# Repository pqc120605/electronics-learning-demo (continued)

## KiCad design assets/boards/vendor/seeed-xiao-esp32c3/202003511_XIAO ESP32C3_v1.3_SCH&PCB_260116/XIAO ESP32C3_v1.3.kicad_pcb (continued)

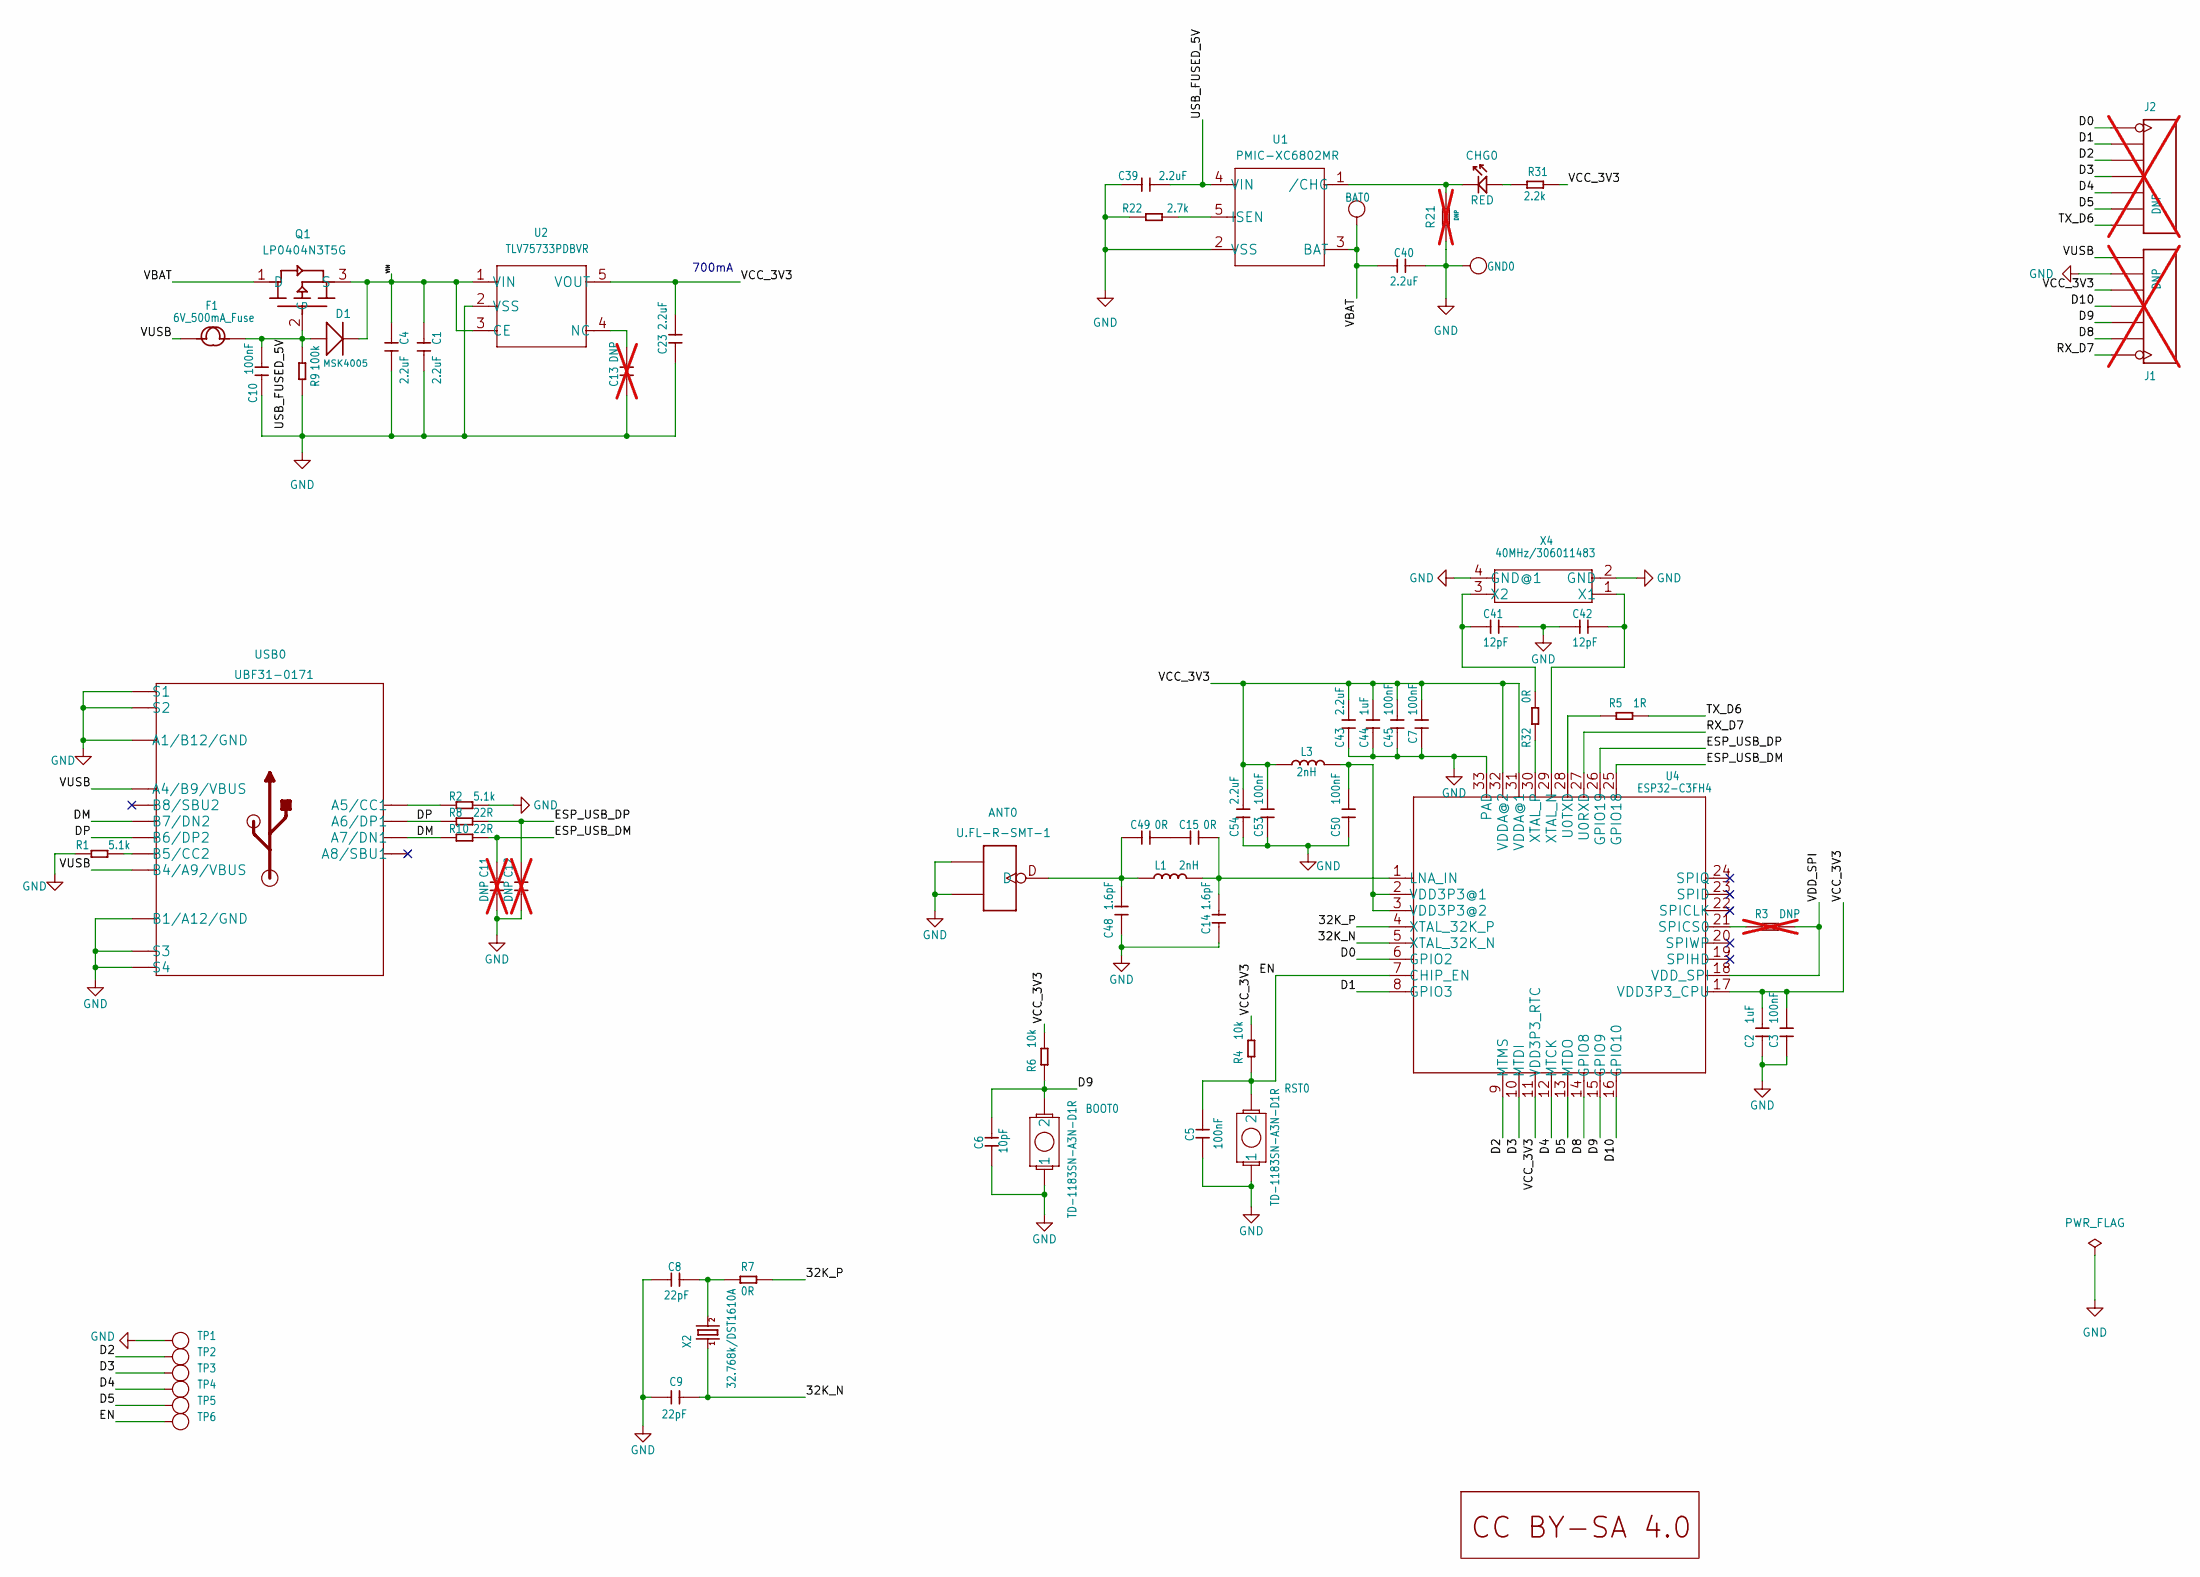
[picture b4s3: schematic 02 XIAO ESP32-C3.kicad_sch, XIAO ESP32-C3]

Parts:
ANT0: U.FL-R-SMT-1; U-FL3P-SMD-2.6X2.6X1.0MM
BAT0: DNP; TP-80X40MIL
BOOT0: TD-1183SN-A3N-D1R; BUTTON_TD1183SA
C1, C4, C23, C39, C40, C43, C54: 2.2uF; C0201
C2, C44: 1uF; C0201
C3, C5, C7, C10, C45, C50, C53: 100nF; C0201
C6: 10pF; C0201
C8, C9: 22pF; C0201
C11, C12, C13: DNP; C0201; not fitted
C14, C48: 1.6pF; C0201
C15, C49: 0R; C0201
C41, C42: 12pF; C0201
CHG0: RED; LED-0402
D1: MSK4005; SOD-523
F1: 6V_500mA_Fuse; F0603
GND0: DNP; TP-80X40MIL
J1, J2: DNP; H7-HALF-HOLE-2.54; not fitted
L1, L3: 2nH; L0201
Q1: LP0404N3T5G; PMOS_1.0_0.6_0.35MM
R1, R2: 5.1k; R0201
R3, R21: DNP; R0201; not fitted
R4, R6: 10k; R0201
R5: 1R; R0201
R7, R32: 0R; R0201
R8, R10: 22R; R0201
R9: 100k; R0201
R22: 2.7k; R0201
R31: 2.2k; R0201
RST0: TD-1183SN-A3N-D1R; BUTTON_TD1183SA
TP1, TP2, TP3, TP4, TP5, TP6: DNP; TP-D45MIL
U1: PMIC-XC6802MR; SOT-25
U2: TLV75733PDBVR; SOT-25
U4: ESP32-C3FH4; QFN32G-0.5-5X5MM
U6: LOGO_CC_BY-SA_4.0
USB0: UBF31-0171; USB2.0-TYPE-C
X2: 32.768k/DST1610A; X2-SMD-1.6X1.0X0.5MM
X4: 40MHz/306011483; X4-SMD-2.0X1.6X0.5MM

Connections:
32K_N: C9.1, U4.5 (XTAL_32K_N), X2.1
32K_P: R7.1, U4.4 (XTAL_32K_P)
D0: J2.1, J2.13 (1), U4.6 (GPIO2)
D1: J2.2, J2.14 (2), U4.8 (GPIO3)
D2: J2.3, J2.15 (3), TP2.T, U4.9 (MTMS)
D3: J2.4, J2.16 (4), TP3.T, U4.10 (MTDI)
D4: J2.5, J2.17 (5), TP4.T, U4.12 (MTCK)
D5: J2.6, J2.18 (6), TP5.T, U4.13 (MTDO)
D8: J1.2, J1.14 (2), U4.14 (GPIO8)
D9: BOOT0.2, C6.2, J1.3, J1.15 (3), R6.1, U4.15 (GPIO9)
D10: J1.4, J1.16 (4), U4.16 (GPIO10)
DM: R10.1, USB0.A7 (A7/DN1), USB0.B7 (B7/DN2)
DP: R8.1, USB0.A6 (A6/DP1), USB0.B6 (B6/DP2)
EN: C5.2, R4.1, RST0.2, TP6.T, U4.7 (CHIP_EN)
ESP_USB_DM: C11.2, R10.2, U4.25 (GPIO18)
ESP_USB_DP: C12.2, R8.2, U4.26 (GPIO19)
GND: ANT0.GND1, ANT0.GND2, BOOT0.1, C1.2, C2.1, C3.1, C4.2, C5.1, C6.1, C7.1, C8.2, C9.2, C10.1, C11.1, C12.1, C13.1, C14.1, C23.1, C39.1, C40.2, C41.2, C42.2, C43.1, C44.1, C45.1, C48.1, C50.1, C53.1, C54.1, GND0.1, J1.6, J1.18 (6), R1.1, R2.2, R9.1, R21.2, R22.2, RST0.1, TP1.T, U1.2 (VSS), U2.2 (VSS), U4.33 (PAD), USB0.A1_B12 (A1/B12/GND), USB0.B1_A12 (B1/A12/GND), USB0.S1, USB0.S2, USB0.S3, USB0.S4, USB0.S5 (S1), USB0.S6 (S2), X4.2 (GND), X4.4 (GND@1)
unnamed: R2.1, USB0.A5 (A5/CC1)
unnamed: R1.2, USB0.B5 (B5/CC2)
unnamed: R3.1, U4.21 (SPICS0)
unnamed: C8.1, R7.2, X2.2
unnamed: C13.2, U2.4 (NC)
unnamed: C15.2, C49.1
unnamed: R22.1, U1.5 (ISEN)
unnamed: CHG0.+, R31.2
unnamed: C14.2, C15.1, L1.2, U4.1 (LNA_IN)
unnamed: C41.1, R32.2, X4.3 (X2)
unnamed: C42.1, U4.29 (XTAL_N), X4.1 (X1)
unnamed: ANT0.D, C48.2, C49.2, L1.1
unnamed: R5.2, U4.28 (U0TXD)
unnamed: C50.2, L3.2, U4.2 (VDD3P3@1), U4.3 (VDD3P3@2)
unnamed: R32.1, U4.30 (XTAL_P)
RX_D7: J1.1, J1.13 (1), U4.27 (U0RXD)
TX_D6: J2.7, J2.19 (7), R5.1
USB_FUSED_5V: C10.2, C39.2, D1.+, F1.2, Q1.2 (G), R9.2, U1.4 (VIN)
VBAT: BAT0.1, C40.1, Q1.1 (D), U1.3 (BAT)
VCC_3V3: C2.2, C3.2, C7.2, C23.2, C43.2, C44.2, C45.2, C53.2, C54.2, J1.5, J1.17 (5), L3.1, R4.2, R6.2, R31.1, U2.5 (VOUT), U4.11 (VDD3P3_RTC), U4.17 (VDD3P3_CPU), U4.31 (VDDA@1), U4.32 (VDDA@2)
VDD_SPI: R3.2, U4.18 (VDD_SPI)
VIN: C1.1, C4.1, D1.-, Q1.3 (S), U2.1 (VIN), U2.3 (CE)
VUSB: F1.1, J1.7, J1.19 (7), USB0.A4_B9 (A4/B9/VBUS), USB0.B4_A9 (B4/A9/VBUS)
~CHG: CHG0.-, R21.1, U1.1 (/CHG)

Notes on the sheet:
700mA

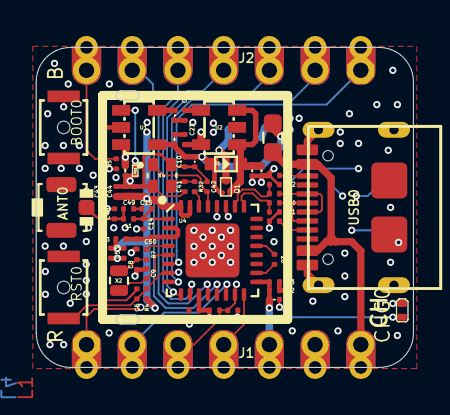
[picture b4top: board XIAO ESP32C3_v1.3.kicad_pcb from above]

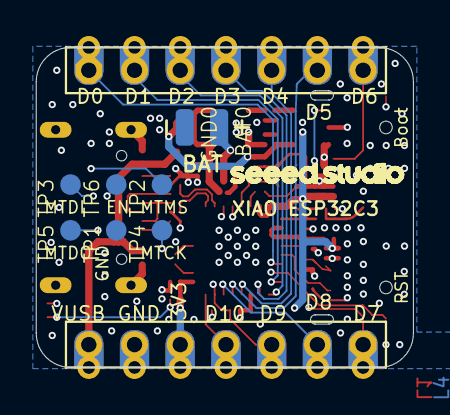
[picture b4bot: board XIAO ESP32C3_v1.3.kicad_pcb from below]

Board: 4 copper layers, 21.0 x 17.8 mm, 68 parts (9 on the bottom side), 41 nets.

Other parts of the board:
U$2: LOGO-SEEED-NEW-1X9.6MM

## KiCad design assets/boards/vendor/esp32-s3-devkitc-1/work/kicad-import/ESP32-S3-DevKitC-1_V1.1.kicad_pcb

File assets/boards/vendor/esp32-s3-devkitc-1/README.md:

# ESP32-S3-DevKitC-1 · PCB V1.1

The board catalog now includes an interactive educational 3D reconstruction of the official V1.1 reference layout.

- 48 CAD footprint/component groups have selectable package meshes.
- 44 J1/J3 header pads have selectable anchors and pinout details.
- BOM manufacturer part numbers are shown when the source BOM identifies them.
- Mesh identity, source coordinates, net-label provenance, and safety caveats are exposed in the board viewer.
- Most meshes are generic package shapes, not exact manufacturer-specific models.

The imported PADS board has DRC findings and unconnected items. The model is not physically validated, not a confirmed N8R8 build, and not suitable for fabrication or electrical sign-off. See [SOURCE.md](SOURCE.md) and the bundled [model notice](/models/esp32-s3-devkitc-1-v1.1.NOTICE.txt).

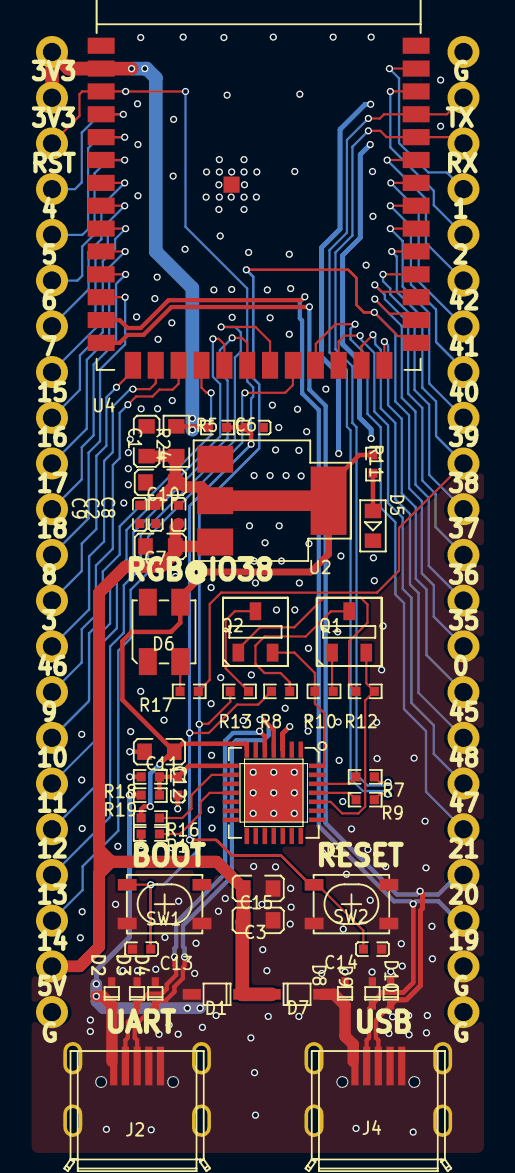
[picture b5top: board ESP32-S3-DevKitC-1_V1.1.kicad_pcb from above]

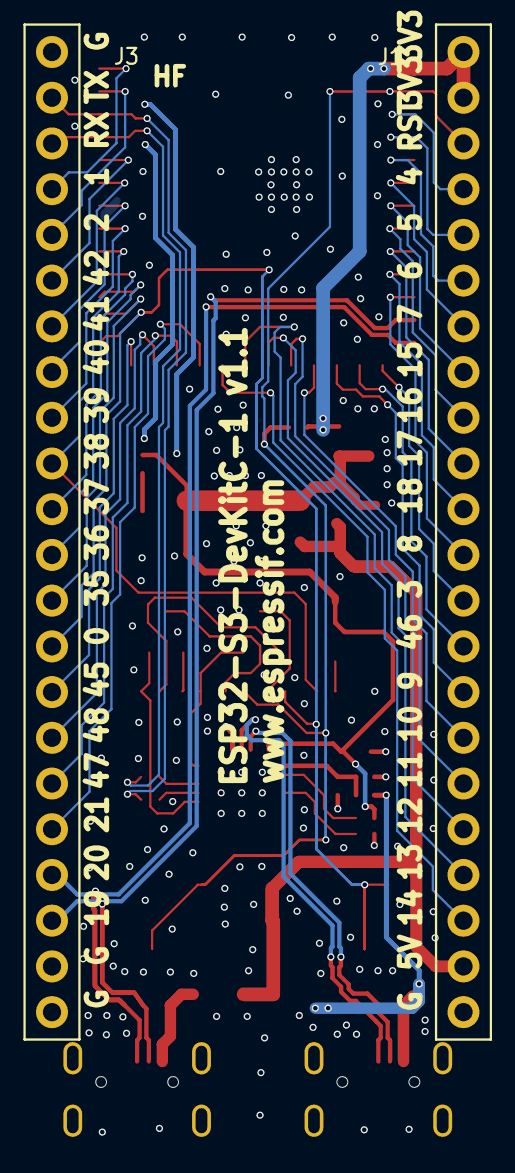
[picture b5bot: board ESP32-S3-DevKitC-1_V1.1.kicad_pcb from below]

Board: 2 copper layers, 48 parts (2 on the bottom side), 58 nets.

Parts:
C1, C3, C7, C10, C11, C15: C0603
C2, C6, C8, C9, C12, C13, C14: C0402
D1, D7: SOD123
D2, D3, D4, D8, D9, D10: SOD523
D5: LED0603
D6: LED3535B
J1, J3: CON22X1_2P54_OBLATE
J2, J4: USB_5P_MICRO_F_ML
Q1, Q2: SOT23-3
R5, R7, R8, R9, R10, R11, R12, R13, R14, R16, R17, R18, R19: R0402
R24: R0603
SW1, SW2: SW4-4P2X3P2X2P5-SMT
U2: SOT223
U3: QFN28_0P5_5
U4: ESP32-S3-WROOM_NEW

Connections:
CHIP_PU: C6.1, C14.2, J1.3, R5.1, R8.2, SW2.3, U4.3
D+: D4.2, J2.3, U3.4
D-: D3.2, J2.2, U3.5
DTR: Q2.2, R10.1, U3.28
ESP_3V3: J1.1, J1.2, R5.2, R24.2, U4.2
GND: C1.2, C2.2, C3.2, C6.2, C7.2, C8.2, C9.2, C10.2, C11.2, C12.2, C13.1, C14.1, C15.2, D2.1, D3.1, D4.1, D5.2, D6.1, D8.1, D9.1, D10.1, J1.22, J2.5, J2.6, J2.7, J2.8, J2.9, J3.1, J3.21, J3.22, J4.5, J4.6, J4.7, J4.8, J4.9, R14.2, R18.2, SW1.1, SW2.1, U2.1, U3.3, U3.29, U4.1, U4.40, U4.41
GPIO0: C13.2, J3.14, R13.2, SW1.3, U4.27
GPIO1: J3.4, U4.39
GPIO2: J3.5, U4.38
GPIO3: J1.13, U4.15
GPIO4: J1.4, U4.4
GPIO5: J1.5, U4.5
GPIO6: J1.6, U4.6
GPIO7: J1.7, U4.7
GPIO8: J1.12, U4.12
GPIO9: J1.15, U4.17
GPIO10: J1.16, U4.18
GPIO11: J1.17, U4.19
GPIO12: J1.18, U4.20
GPIO13: J1.19, U4.21
GPIO14: J1.20, U4.22
GPIO15: J1.8, U4.8
GPIO16: J1.9, U4.9
GPIO17: J1.10, U4.10
GPIO18: J1.11, U4.11
GPIO19: D9.2, J3.20, J4.2, U4.13
GPIO20: D10.2, J3.19, J4.3, U4.14
GPIO21: J3.18, U4.23
GPIO35: J3.13, U4.28
GPIO36: J3.12, U4.29
GPIO37: J3.11, U4.30
GPIO38: J3.10, R17.1, U4.31
GPIO39: J3.9, U4.32
GPIO40: J3.8, U4.33
GPIO41: J3.7, U4.34
GPIO42: J3.6, U4.35
GPIO45: J3.15, U4.26
GPIO46: J1.14, U4.16
GPIO47: J3.17, U4.24
GPIO48: J3.16, U4.25
N17688270: C12.1, R18.1, R19.2, U3.8
N17688616: R16.1, U3.9
N17688663: R14.1, U3.11
N17689011: R7.1, U3.26
N17689016: R9.1, U3.25
N17689859: Q1.1, R10.2
N17689862: Q2.1, R12.2
N17689962: Q2.3, R13.1
N17689967: Q1.3, R8.1
N17692194: D5.1, R11.2
RGB_CTRL: D6.2, R17.2
RTS: Q1.2, R12.1, U3.24
U0RXD: J3.3, R7.2, U4.36
U0TXD: J3.2, R9.2, U4.37
VBUS: D1.1, D2.2, J2.1, R19.1
VBUSB: D7.1, D8.2, J4.1
VCC_3V3: C1.1, C2.1, C9.1, C10.1, C11.1, D6.3, R11.1, R16.2, R24.1, U2.2, U2.4, U3.6, U3.7
VCC_5V: C3.1, C7.1, C8.1, C15.1, D1.2, D7.2, J1.21, U2.3

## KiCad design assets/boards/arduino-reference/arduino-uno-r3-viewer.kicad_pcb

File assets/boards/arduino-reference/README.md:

# Arduino reference board models

## Current web assets

The public Uno, Nano classic and Mega 2560 R3 GLBs are exported from imported board CAD files. They include PCB artwork and package bodies linked to footprints. The generator aligns package bodies by fitting KiCad footprint pad geometry to numbered pads in the imported footprint; it supports mirrored local Y frames and maps verified common package aliases.

Through-hole header footprints are intentionally left unpopulated in the 3D model. The reference CAD identifies solder pads, not whether male/female headers are fitted. This removes unsupported floating connector bodies while preserving the actual pads. Missing 3D bodies remain visible as pads/footprints instead of guessed geometry. USB shells are not pad-fitted because mechanical mounting tabs vary across connector models. Model nodes retain footprint reference names for component hover/selection.

KiCad package bodies depict standard package geometry, not manufacturer-specific scans, markings, or proof that an individual clone uses the exact part. Passive bodies can differ from the physical component while remaining aligned to the CAD footprint. The Nano source schematic names IC3 as ATmega328P-32MUR, matching the QFN/VQFN body used here; this is not the TQFP Nano package variant. Pin coordinate picking is disabled until anchors are mapped to actual pads.

| Board | KiCad import | Web GLB | Source reference |
|---|---|---|---|
| Arduino Uno R3 | `arduino-uno-r3-official-import.kicad_pcb` | `public/models/arduino-uno-r3.glb` | `upstream-cad/UNO-TH_Rev3e.brd` |
| Arduino Nano classic | `arduino-nano-classic-official-import.kicad_pcb` | `public/models/arduino-nano-classic.glb` | `upstream-cad/nano-classic/A00005-cad-files/NanoV3.3.brd` |
| Arduino Mega 2560 R3 | `arduino-mega-2560-r3-official-import.kicad_pcb` | `public/models/arduino-mega-2560-r3.glb` | `upstream-cad/mega-2560-r3/A000067-cad-files/MEGA2560_Rev3e.brd` |

## Re-export

Run `attach_reference_models.py` to regenerate separate model-bearing KiCad boards from the preserved imports. Export each `*-viewer.kicad_pcb` with KiCad CLI to its matching `public/models/*.glb` file. Increment the corresponding version in `src/data/arduinoBoardModels.ts` to bust browser cache. The current public models are version 3.4.0.

## Source and attribution

- Uno source: Arduino Uno Rev3 CAD files supplied in this project; see `upstream-cad/License.txt`.
- Nano source: [Arduino Nano documentation](https://docs.arduino.cc/hardware/nano/) and included archive license.
- Mega source: [Arduino Mega 2560 Rev3 documentation](https://docs.arduino.cc/hardware/mega-2560/) and included archive license.
- The Arduino hardware design archives include CC BY-SA 4.0 licensing. Retain attribution and share-alike terms when distributing derivatives; review each included license.
- KiCad package 3D models: [KiCad 3D model license](https://github.com/KiCad/kicad-packages3D/blob/master/LICENSE.md).

## Remaining CAD work

The interactive lesson currently has eight board reference models: ESP32 DevKit V1, Uno R3, Nano classic, Mega 2560 R3, three Raspberry Pi Pico-family boards and one community Blue Pill-style design. Arduino GLBs were regenerated to align supported package bodies and remove unsupported fitted headers. Other catalog entries (ESP32-C3, ESP32-S3 and NUCLEO-F401RE) remain previews, not interactive 3D boards. ESP32-S3 source CAD exists locally as PADS ASCII, but KiCad's Non-KiCad Board importer rejects this `.asc` file as unsupported. It has not been converted, fitted with package bodies, checked against source placement/BOM, or cleared for redistribution as a derived educational asset. The NUCLEO-F401RE Altium project is present locally but has not been converted and validated. Do not add a preview to the lesson selector until its GLB and component references are validated. The earlier `generate_boards.py` creates rough placeholders and is no longer the source of public Arduino GLBs.

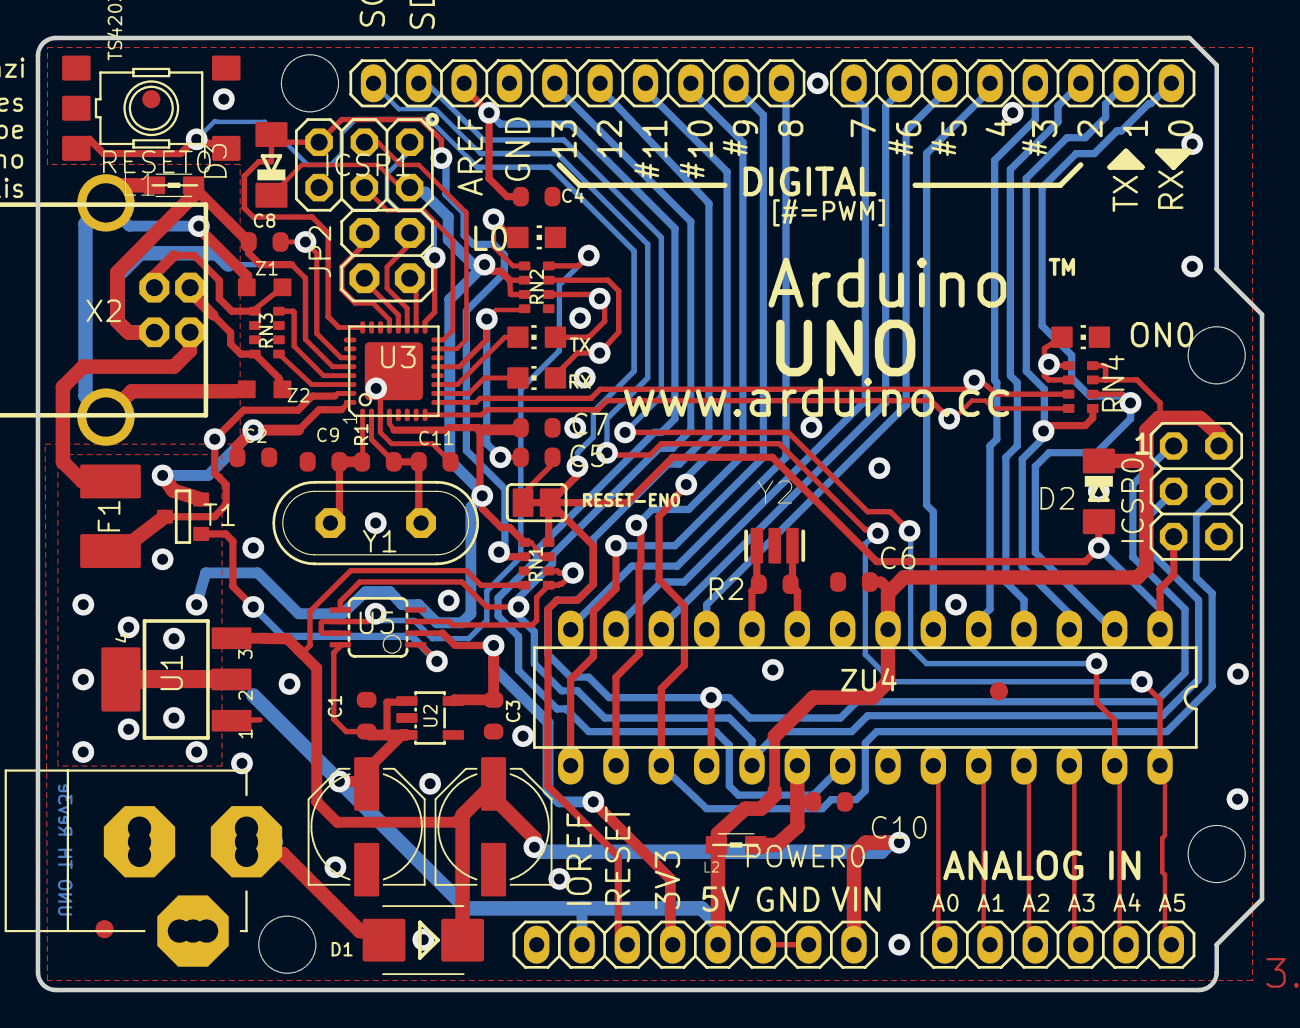
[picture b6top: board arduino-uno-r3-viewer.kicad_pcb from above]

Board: 2 copper layers, 68.6 x 53.3 mm, 120 parts (1 on the bottom side), 61 nets.

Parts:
AD0: 6x1F-H8.5; 1X06
C1, C2, C4, C5, C6, C7, C10: 100n; C0603-ROUND
C3, C8: 1u; C0603-ROUND
C9, C11: 22p; C0603-ROUND
D1: M7; SMB
D2, D3: CD1206-S01575; MINIMELF
F1: MF-MSMF050-2 500mA; L1812
FD1, FD2, FD3: FIDUCIALMOUNT; FIDUCIA-MOUNT
FRAME1: DNP; FRAME
GND_TP0, GND_TP1: TP_SP; TP-SP
GROUND0: SJ
ICSP0, ICSP1: 3x2 M; 2X03
IOH0: 10x1F-H8.5; 1X10
IOL0: 8x1F-H8.5; 1X08
JP2: 2x2 M - NM; 2X02
L0: YELLOW; CHIP-LED0805
L1: BLM21; 0805
L2: 10uH; 0805
ON0: GREEN; CHIP-LED0805
ORIGIN0: TP_SP; TP-SP
PC1, PC2: 47u; PANASONIC_D
POWER0: 8x1F-H8.5; 1X08
R1, R2: 1M; R0603-ROUND
RESET0: TS42031-160R-TR-7260; TS42
RESET-EN0: SJ
RN1: 10K; CAY16
RN2, RN4: 1K; CAY16
RN3: 22R; CAY16
RX0: YELLOW; CHIP-LED0805
T1: FDN340P; SOT-23
TP_0, TP_1, TP_2, TP_3, TP_3V3, TP_4, TP_5, TP_5V0, TP_5V1, TP_6, TP_7, TP_8, TP_9, TP_10, TP_11, TP_12, TP_13: TP_SP; TP-SP
TP_A0, TP_A1, TP_A2, TP_A3, TP_A4, TP_A5: TP_SP; TP-SP
TP_AREF0: TP_SP; TP-SP
TP_CMP0: TP_SP; TP-SP
TP_D+0: TP_SP; TP-SP
TP_D-0: TP_SP; TP-SP
TP_DTR0: TP_SP; TP-SP
TP_GATE0: TP_SP; TP-SP
TP_LCMD0: TP_SP; TP-SP
TP_LL0: TP_SP; TP-SP
TP_MISO2: TP_SP; TP-SP
TP_MOSI2: TP_SP; TP-SP
TP_ONL0: TP_SP; TP-SP
TP_PB4, TP_PB5, TP_PB6, TP_PB7: TP_SP; TP-SP
TP_PWRIN0: TP_SP; TP-SP
TP_RESET0, TP_RESET2: TP_SP; TP-SP
TP_RX0: TP_SP; TP-SP
TP_RXL0: TP_SP; TP-SP
TP_SCK2: TP_SP; TP-SP
TP_SCL0: TP_SP; TP-SP
TP_SDA0: TP_SP; TP-SP
TP_TX0: TP_SP; TP-SP
TP_TXL0: TP_SP; TP-SP
TP_UGND0: TP_SP; TP-SP
TP_USBVCC0: TP_SP; TP-SP
TP_USH0: TP_SP; TP-SP
TP_VIN0: TP_SP; TP-SP
TP_VUCAP0: TP_SP; TP-SP
TP_XT1, TP_XT2, TP_XT3, TP_XT4: TP_SP; TP-SP
TP_XUSB0: TP_SP; TP-SP
TX0: YELLOW; CHIP-LED0805
U1: NCP1117ST50T3G; SOT223
U2: LP2985-33DBVR; SOT23-DBV
U3: ATMEGA16U2-MU(R); MLF32
U5: LMV358IDGKR; MSOP08
UNK_HOLE_0: dummyfp0
UNK_HOLE_1: dummyfp1
UNK_HOLE_2: dummyfp2
UNK_HOLE_3: dummyfp3
X1: POWERSUPPLY_DC21MMX; POWERSUPPLY_DC-21MM
X2: USB-B_TH; PN61729
Y1: 16MHz; QS
Y2: CSTCE16M0V53-R0 16MHZ; RESONATOR
Z1, Z2: CG0603MLC-05E; CT_CN0603
ZU4: ATMEGA328P-PU; DIL28-3

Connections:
+3V3: C3.2, POWER0.4, TP_3V3.X, U2.5, U5.2
+5V: C1.2, C2.2, C6.2, C7.1, D2.C, D3.C, ICSP0.2, ICSP1.2, L2.1, PC2.+, POWER0.2, POWER0.5, RN1.3, RN1.5, RN2.2, RN2.3, RN4.3, RN4.4, T1.2, TP_5V0.X, TP_5V1.X, U1.2, U1.4, U2.1, U2.3, U3.4, U3.32, U5.8, ZU4.7
AD0: AD0.1, TP_A0.X, ZU4.23
AD1: AD0.2, TP_A1.X, ZU4.24
AD2: AD0.3, TP_A2.X, ZU4.25
AD3: AD0.4, TP_A3.X, ZU4.26
AD4/SDA: AD0.5, IOH0.9, TP_A4.X, TP_SDA0.X, ZU4.27
AD5/SCL: AD0.6, IOH0.10, TP_A5.X, TP_SCL0.X, ZU4.28
AREF: C4.2, IOH0.8, TP_AREF0.X, ZU4.21
AVCC: C10.2, L2.2, ZU4.20
CMP: RN1.1, RN1.2, TP_CMP0.X, U5.3
D+: RN3.5, TP_D+0.X, X2.3, Z1.1
D-: RN3.8, TP_D-0.X, X2.2, Z2.1
DTR: C5.1, RN2.4, TP_DTR0.X, U3.13
GATE_CMD: T1.3, TP_GATE0.X, U5.1
GND: C1.1, C2.1, C3.1, C4.1, C6.1, C7.2, C9.2, C10.1, C11.2, GND_TP0.X, GND_TP1.X, GROUND0.1, ICSP0.6, ICSP1.6, IOH0.7, L0.C, ON0.C, PC1.-, PC2.-, POWER0.6, POWER0.7, RESET0.1, RESET0.2, RN1.7, RN2.5, U1.1, U2.2, U3.3, U3.33, U5.4, X1.1, X1.3, Y2.2, ZU4.8, ZU4.22
IO0: IOL0.1, RN4.2, TP_0.X, ZU4.2
IO1: IOL0.2, RN4.1, TP_1.X, ZU4.3
IO2: IOL0.3, TP_2.X, ZU4.4
IO3: IOL0.4, TP_3.X, ZU4.5
IO4: IOL0.5, TP_4.X, ZU4.6
IO5: IOL0.6, TP_5.X, ZU4.11
IO6: IOL0.7, TP_6.X, ZU4.12
IO7: IOL0.8, TP_7.X, ZU4.13
IO8: IOH0.1, TP_8.X, ZU4.14
IO9: IOH0.2, TP_9.X, ZU4.15
L13: RN2.8, TP_LCMD0.X, U5.6, U5.7
M8RXD: RN4.7, TP_RX0.X, U3.9
M8TXD: RN4.8, TP_TX0.X, U3.8
MISO: ICSP0.1, IOH0.5, TP_12.X, ZU4.18
MISO2: ICSP1.1, TP_MISO2.X, U3.17
MOSI: ICSP0.4, IOH0.4, TP_11.X, ZU4.17
MOSI2: ICSP1.4, TP_MOSI2.X, U3.16
unnamed: L0.A, RN2.1, TP_LL0.X
unnamed: ON0.A, RN4.5, RN4.6, TP_ONL0.X
unnamed: RN2.7, RX0.A, TP_RXL0.X
unnamed: RN2.6, TP_TXL0.X, TX0.A
PB4: JP2.1, TP_PB4.X, U3.18
PB5: JP2.3, TP_PB5.X, U3.19
PB6: JP2.2, TP_PB6.X, U3.20
PB7: JP2.4, TP_PB7.X, U3.21
PWRIN: D1.A, TP_PWRIN0.X, X1.2
RD+: RN3.4, U3.29
RD-: RN3.1, U3.30
RESET: C5.2, D2.A, ICSP0.5, POWER0.3, RESET0.3, RESET0.4, RESET-EN0.1, RESET-EN0.2, RN1.4, TP_RESET0.X, ZU4.1
RESET2: D3.A, ICSP1.5, RN1.6, TP_RESET2.X, U3.24
RXLED: RX0.C, U3.10
SCK: ICSP0.3, IOH0.6, TP_13.X, U5.5, ZU4.19
SCK2: ICSP1.3, TP_SCK2.X, U3.15
SS: IOH0.3, TP_10.X, ZU4.16
TP_VUCAP: C8.1, TP_VUCAP0.X, U3.27
TXLED: TX0.C, U3.11
UGND: C8.2, GROUND0.2, L1.1, TP_UGND0.X, U3.28, X2.4
USBVCC: F1.1, T1.1, TP_USBVCC0.X, U3.31
USHIELD: L1.2, TP_USH0.X, X2.P$1, X2.P$2, Z1.2, Z2.2
VIN: D1.C, PC1.+, POWER0.8, RN1.8, TP_VIN0.X, U1.3
XT1: C9.1, R1.1, TP_XT3.X, U3.1, Y1.2
XT2: C11.1, R1.2, TP_XT4.X, U3.2, Y1.1
XTAL1: R2.1, TP_XT1.X, Y2.3, ZU4.9
XTAL2: R2.2, TP_XT2.X, Y2.1, ZU4.10
XUSB: F1.2, TP_XUSB0.X, X2.1

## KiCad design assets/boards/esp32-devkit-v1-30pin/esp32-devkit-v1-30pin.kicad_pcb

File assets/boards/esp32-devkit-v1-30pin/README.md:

# ESP32 Dev Kit Clone 30-pin reference model

The web model now comes from the supplied KiCad design, rather than the earlier generated approximation. The chosen source is the open ESP32 Dev Kit Clone project by Brij Modi. Its board is 2-layer and measures about 47.06 × 29.23 mm. It is a specific educational reference design; “ESP32 DevKit V1” clones sold by different vendors may not match its layout, components, or pin order.

## Source files

- `upstream/ESP32 Dev Kit.kicad_pcb` and `.kicad_sch` are the supplied upstream board and schematic.
- `upstream/Connectors.kicad_sch` is the schematic sheet for connectors.
- `esp32-devkit-v1-30pin.kicad_pcb` is the normalized working copy used for exports. The PCB layout, nets, routing, component values, and board outline are preserved from upstream.
- `prepare_reference_board.py` replaces the author's machine-specific CP2102 STEP path with KiCad's standard 5 × 5 mm QFN-28 package model. This generic shell shows the correct package form and size but not the CP2102 top marking.
- The stock KiCad QFN model uses the board coordinate convention. The source CP2102 footprint carried a legacy X=-90° transform for its vendor model; `prepare_reference_board.py` now clears that rotation, offset, and scale when substituting the KiCad package. `correct_cp2102_glb_orientation.py` applies the same correction to an already-exported GLB without changing its geometry buffers.
- `../../../../public/models/esp32-devkit-v1-30pin.glb` is exported from the working PCB with KiCad 9.
- `../../../../public/models/esp32-led-assembly.glb` adds the lesson breadboard, external LED, resistor, and illustrative wires. Those external objects are educational geometry; they are not part of the board schematic or an electrical simulation.

The upstream README declares the board project MIT-licensed. The archive did not contain a separate `LICENSE` file, so preserve author attribution and the upstream repository link if redistributing the design. KiCad stock footprint 3D models use KiCad's published license and exception; see the [KiCad footprint license](https://github.com/KiCad/kicad-footprints/blob/master/LICENSE.md) and [KiCad 3D model license](https://github.com/KiCad/kicad-packages3D/blob/master/LICENSE.md).

## Rebuild the reference GLB

Run in PowerShell from this directory on a machine with KiCad 9 and its standard 3D model library installed:

```powershell
& 'C:\Program Files\KiCad\9.0\bin\python.exe' .\prepare_reference_board.py
& 'C:\Program Files\KiCad\9.0\bin\kicad-cli.exe' pcb export glb --force --subst-models --include-silkscreen --output '..\..\..\public\models\esp32-devkit-v1-30pin.glb' '.\esp32-devkit-v1-30pin.kicad_pcb'
python ..\..\..\assets\boards\esp32-devkit-v1-30pin\compose_led_assembly.py
```

The viewer manifest is in `src/data/esp32DevkitModel.ts`. Its hotspot node names are KiCad footprint references (U1, J1, U2, U3, SW1, SW2, J2, J3, D1, D2, R1–R6, C1–C6, Q1, Q2). Pin anchors use the actual pad centers from J2/J3. Recheck them whenever the source layout or exported GLB changes.

## Electrical-path notes

The board schematic connects USB VBUS through D1 to the AMS1117 regulator input, then distributes 3.3 V to the ESP32 module. USB D+/D− go to the CP2102; its UART connects to ESP32 RX0/TX0. DTR/RTS drive Q1/Q2 for automatic BOOT/EN control. SW1 pulls Boot low, SW2 pulls EN low, and J2 pad 15 is GPIO23. These explanations describe the supplied schematic/netlist. The browser viewer displays geometry and explanatory paths; it does not simulate current, firmware, or electrical behavior.

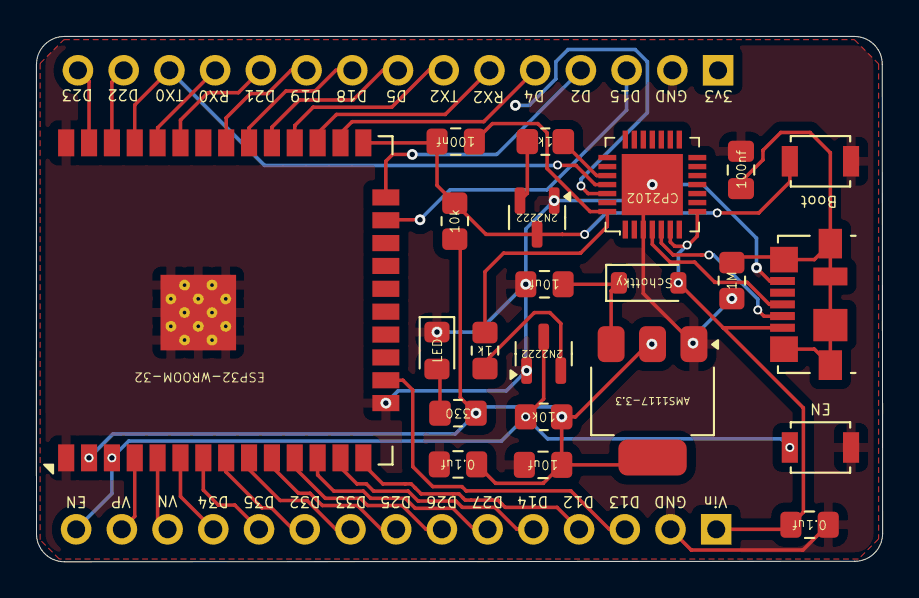
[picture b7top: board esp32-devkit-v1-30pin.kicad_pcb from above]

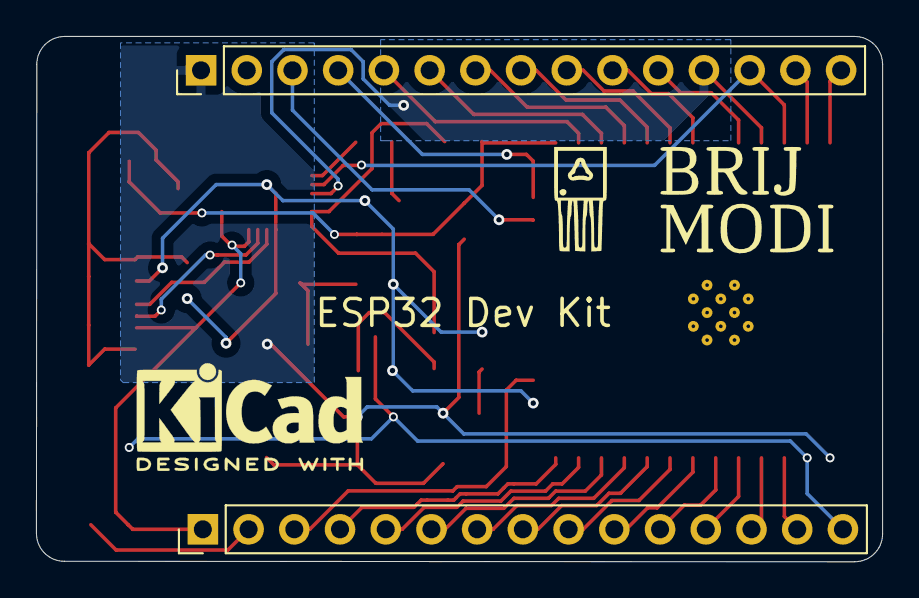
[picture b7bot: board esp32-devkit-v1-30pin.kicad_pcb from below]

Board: 2 copper layers, 47.0 x 29.2 mm, 24 parts (2 on the bottom side), 39 nets.

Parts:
C1, C2: 10uf; C_0805_2012Metric_Pad1.18x1.45mm_HandSolder
C3, C5: 0.1uf; C_0805_2012Metric_Pad1.18x1.45mm_HandSolder
C4, C6: 100nf; C_0805_2012Metric_Pad1.18x1.45mm_HandSolder
D1: D_Schottky; D_SOD-123
D2: LED; LED_0805_2012Metric_Pad1.15x1.40mm_HandSolder
J1: USB_B_Micro; USB_Micro-B_Molex_47346-0001
J2, J3: Conn_01x15; PinHeader_1x15_P2.54mm_Vertical
Q1, Q2: 2N2222; SOT-23
R1: 330; R_0805_2012Metric_Pad1.20x1.40mm_HandSolder
R2, R5: 10k; R_0805_2012Metric_Pad1.20x1.40mm_HandSolder
R3: 1M; R_0805_2012Metric_Pad1.20x1.40mm_HandSolder
R4, R6: 1k; R_0805_2012Metric_Pad1.20x1.40mm_HandSolder
SW1, SW2: SW_Push; SW_SPST_B3U-1000P
U1: ESP32-WROOM-32
U2: AMS1117-3.3; SOT-223-3_TabPin2
U3: CP2102-GMR_NRND; VFQFN-28-1EP_5x5mm

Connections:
/3.3v: C2.1, C3.1, J2.1, R1.1, R2.1, R5.1, U1.2 (VDD), U2.2 (VO)
/5v: C5.1, D1.2 (A), J1.1 (VBUS), J3.1, U3.6 (VDD), U3.8 (VBUS)
/Boot: C6.2, Q1.3 (C), R2.2, SW1.1, U1.25 (IO0)
/D2: J2.4, U1.24 (IO2)
/D4: J2.5, U1.26 (IO4)
/D5: J2.8, U1.29 (IO5)
/D12: J3.4, U1.14 (IO12)
/D13: J3.3, U1.16 (IO13)
/D14: J3.5, U1.13 (IO14)
/D15: J2.3, U1.23 (IO15)
/D18: J2.9, U1.30 (IO18)
/D19: J2.10, U1.31 (IO19)
/D21: J2.11, U1.33 (IO21)
/D22: J2.14, U1.36 (IO22)
/D23: J2.15, U1.37 (IO23)
/D25: J3.8, U1.10 (IO25)
/D26: J3.7, U1.11 (IO26)
/D27: J3.6, U1.12 (IO27)
/D32: J3.10, U1.8 (IO32)
/D33: J3.9, U1.9 (IO33)
/D34: J3.12, U1.6 (IO34)
/D35: J3.11, U1.7 (IO35)
/DTR: C6.1, R6.1, U3.28 (DTR)
/EN: J3.15, Q2.3 (C), R5.2, SW2.1, U1.3 (EN)
/RTS: R4.1, U3.24 (RTS)
/RX0: J2.12, U1.34 (RXD0/IO3), U3.26 (TXD)
/RX2: J2.6, U1.27 (IO16)
/TX0: J2.13, U1.35 (TXD0/IO1), U3.25 (RXD)
/TX2: J2.7, U1.28 (IO17)
/VN: J3.13, U1.5 (SENSOR_VN)
/VP: J3.14, U1.4 (SENSOR_VP)
GND: C1.2, C2.2, C3.2, C4.2, C5.2, D2.1 (K), J1.5 (GND), J2.2, J3.2, Q1.1 (E), Q2.1 (E), R3.2, SW1.2, SW2.2, U1.1 (GND), U1.15 (GND), U1.38 (GND), U1.39 (GND), U2.1 (GND), U3.3 (GND), U3.29 (GND_PAD)
unnamed: C1.1, D1.1 (K), U2.3 (VI)
unnamed: D2.2 (A), R1.2
unnamed: J1.3 (D+), U3.4 (D+)
unnamed: J1.2 (D-), U3.5 (D-)
unnamed: C4.1, J1.6 (Shield), R3.1
unnamed: Q1.2 (B), R4.2
unnamed: Q2.2 (B), R6.2

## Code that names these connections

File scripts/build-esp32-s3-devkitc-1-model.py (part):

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    "J4": ("Micro-USB connector J4", "Native USB connector; generic package mesh, not an exact manufacturer-specific body.", "source-backed"),
    "SW1": ("BOOT button", "Boot-mode button per the official board guide.", "source-backed"),
    "SW2": ("RESET button", "Reset/enable button per the official board guide.", "source-backed"),
    "D6": ("Addressable RGB LED · GPIO38", "V1.1 board guide identifies the RGB LED on GPIO38; package mesh is a 3.5 mm generic outline.", "source-backed"),
    "D5": ("Red indicator LED", "Red indicator LED per BOM; do not infer electrical behavior beyond the CAD/BOM.", "source-backed"),
    "D1": ("Schottky diode · SOD-123", "Part family from BOM; generic package mesh.", "source-backed"),
    "D2": ("ESD protection diode · SOD-523", "BOM identifies a 5 V ESD diode; generic package mesh.", "source-backed"),
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}

PIN_LABELS = {
    "J1": ["3V3", "3V3", "EN", "GPIO4", "GPIO5", "GPIO6", "GPIO7", "GPIO15", "GPIO16", "GPIO17", "GPIO18", "GPIO8", "GPIO3", "GPIO46", "GPIO9", "GPIO10", "GPIO11", "GPIO12", "GPIO13", "GPIO14", "5V", "GND"],
    "J3": ["GND", "TX/GPIO43", "RX/GPIO44", "GPIO1", "GPIO2", "GPIO42", "GPIO41", "GPIO40", "GPIO39", "GPIO38", "GPIO37", "GPIO36", "GPIO35", "GPIO0", "GPIO45", "GPIO48", "GPIO47", "GPIO21", "GPIO20", "GPIO19", "GND", "GND"],
}


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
